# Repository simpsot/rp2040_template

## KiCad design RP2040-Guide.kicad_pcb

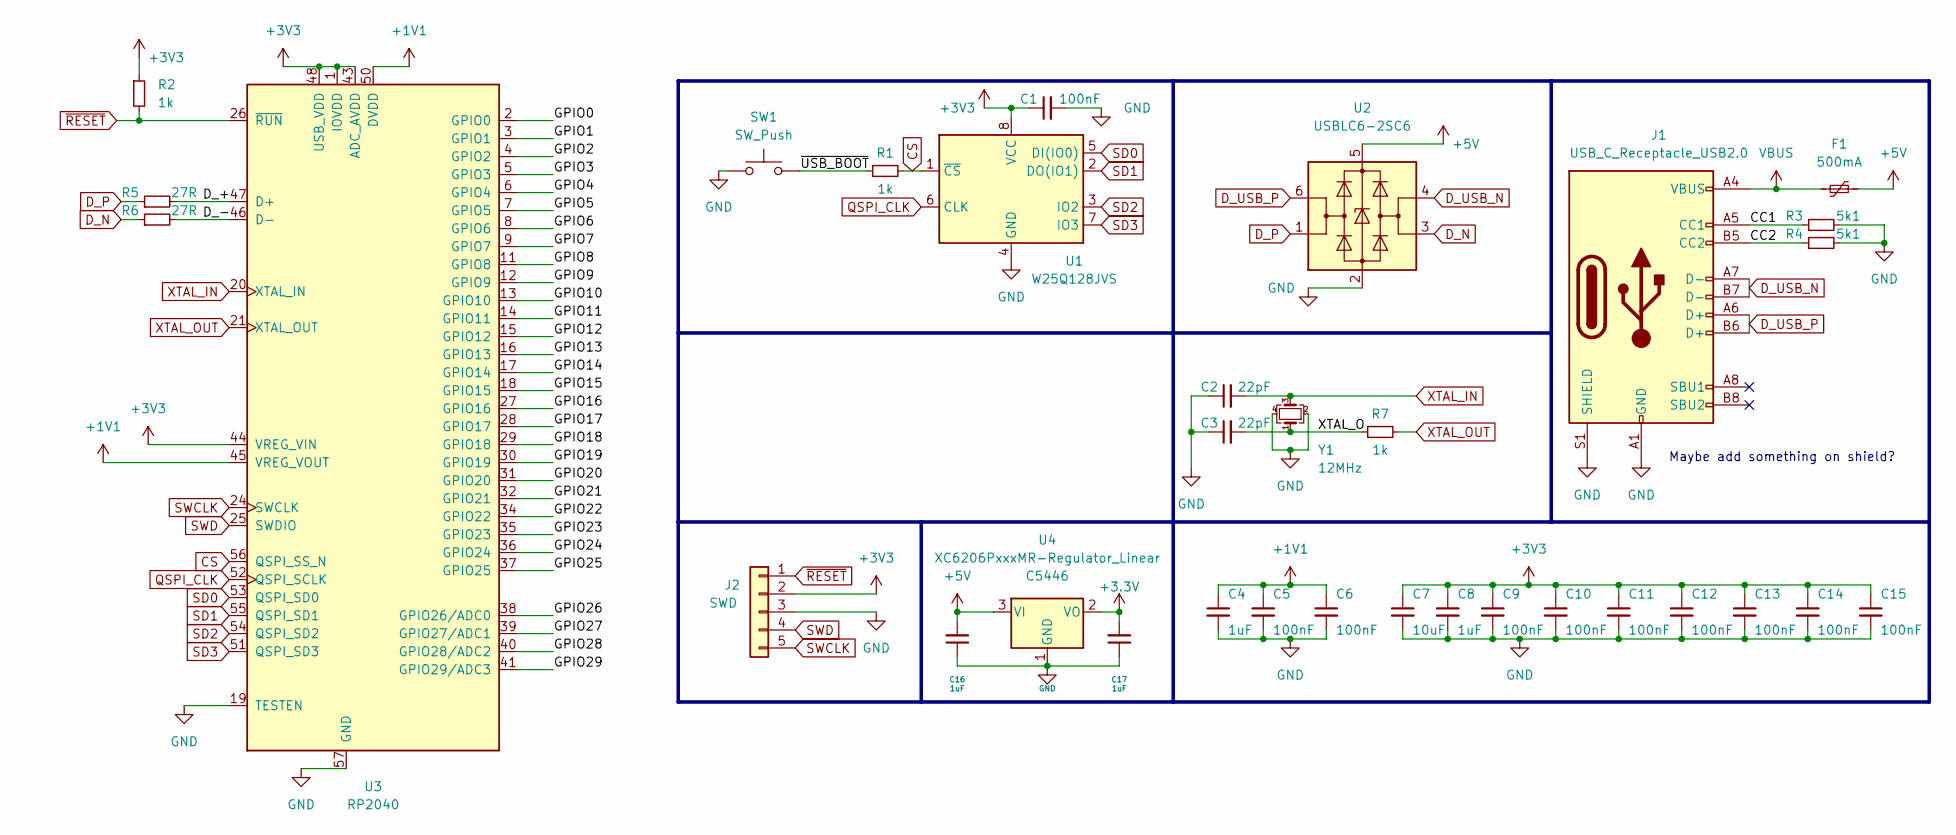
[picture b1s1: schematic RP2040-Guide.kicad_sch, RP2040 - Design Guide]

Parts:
C1, C5, C6, C9, C10, C11, C12, C13, C14, C15: 100nF; C_0402_1005Metric; LCSC C1525
C2, C3: 22pF; C_0402_1005Metric; LCSC C1555
C4, C8, C16, C17: 1uF; C_0402_1005Metric; LCSC C52923
C7: 10uF; C_0402_1005Metric; LCSC C15525
F1: 500mA; Fuse_1206_3216Metric; LCSC C70076
J1: USB_C_Receptacle_USB2.0; USB_C_Receptacle_HRO_TYPE-C-31-M-12; LCSC C165948
J2: SWD; PinSocket_1x05_P2.54mm_Vertical
R1, R2, R7: 1k; R_0402_1005Metric; LCSC C11702
R3, R4: 5k1; R_0402_1005Metric; LCSC C25905
R5, R6: 27R; R_0603_1608Metric; LCSC C25190
SW1: SW_Push; PinSocket_1x02_P2.54mm_Vertical
U1: W25Q128JVS; SOIC-8_5.23x5.23mm_P1.27mm; LCSC C131025
U2: USBLC6-2SC6; SOT-23-6; LCSC C2827654
U3: RP2040; RP2040-QFN-56; LCSC C2040
U4: XC6206PxxxMR-Regulator_Linear; SOT-23; LCSC C5446
Y1: 12MHz; Crystal_SMD_3225-4Pin_3.2x2.5mm; LCSC C9002

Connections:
+1V1: C4.1, C5.1, C6.1, U3.23 (DVDD), U3.45 (VREG_VOUT), U3.50 (DVDD)
+5V: C16.2, F1.2, U2.5 (VBUS), U4.3 (VI)
/CC1: J1.A5 (CC1), R3.1
/CC2: J1.B5 (CC2), R4.1
/D_+: R5.2, U3.47 (D+)
/D_-: R6.2, U3.46 (D-)
/GPIO0: U3.2 (GPIO0)
/GPIO1: U3.3 (GPIO1)
/GPIO2: U3.4 (GPIO2)
/GPIO3: U3.5 (GPIO3)
/GPIO4: U3.6 (GPIO4)
/GPIO5: U3.7 (GPIO5)
/GPIO6: U3.8 (GPIO6)
/GPIO7: U3.9 (GPIO7)
/GPIO8: U3.11 (GPIO8)
/GPIO9: U3.12 (GPIO9)
/GPIO10: U3.13 (GPIO10)
/GPIO11: U3.14 (GPIO11)
/GPIO12: U3.15 (GPIO12)
/GPIO13: U3.16 (GPIO13)
/GPIO14: U3.17 (GPIO14)
/GPIO15: U3.18 (GPIO15)
/GPIO16: U3.27 (GPIO16)
/GPIO17: U3.28 (GPIO17)
/GPIO18: U3.29 (GPIO18)
/GPIO19: U3.30 (GPIO19)
/GPIO20: U3.31 (GPIO20)
/GPIO21: U3.32 (GPIO21)
/GPIO22: U3.34 (GPIO22)
/GPIO23: U3.35 (GPIO23)
/GPIO24: U3.36 (GPIO24)
/GPIO25: U3.37 (GPIO25)
/GPIO26: U3.38 (GPIO26/ADC0)
/GPIO27: U3.39 (GPIO27/ADC1)
/GPIO28: U3.40 (GPIO28/ADC2)
/GPIO29: U3.41 (GPIO29/ADC3)
/XTAL_O: C3.2, R7.1, Y1.1
/~USB_BOOT: R1.1, SW1.2
CS: R1.2, U1.1 (~CS), U3.56 (QSPI_SS_N)
D_N: R6.1, U2.3 (I/O2)
D_P: R5.1, U2.1 (I/O1)
D_USB_N: J1.A7 (D-), J1.B7 (D-), U2.4 (I/O2)
D_USB_P: J1.A6 (D+), J1.B6 (D+), U2.6 (I/O1)
GND: C1.2, C2.1, C3.1, C4.2, C5.2, C6.2, C7.2, C8.2, C9.2, C10.2, C11.2, C12.2, C13.2, C14.2, C15.2, C16.1, C17.1, J1.A1 (GND), J1.A12 (GND), J1.B1 (GND), J1.B12 (GND), J1.S1 (SHIELD), J2.3, R3.2, R4.2, SW1.1, U1.4 (GND), U2.2 (GND), U3.19 (TESTEN), U3.57 (GND), U4.1 (GND), Y1.2, Y1.4
QSPI_CLK: U1.6 (CLK), U3.52 (QSPI_SCLK)
SD0: U1.5 (DI(IO0)), U3.53 (QSPI_SD0)
SD1: U1.2 (DO(IO1)), U3.55 (QSPI_SD1)
SD2: U1.3 (IO2), U3.54 (QSPI_SD2)
SD3: U1.7 (IO3), U3.51 (QSPI_SD3)
SWCLK: J2.5, U3.24 (SWCLK)
SWD: J2.4, U3.25 (SWDIO)
VBUS: F1.1, J1.A4 (VBUS), J1.A9 (VBUS), J1.B4 (VBUS), J1.B9 (VBUS)
XTAL_IN: C2.2, U3.20 (XTAL_IN), Y1.3
XTAL_OUT: R7.2, U3.21 (XTAL_OUT)
~RESET: J2.1, R2.2, U3.26 (~RUN)

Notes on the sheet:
Maybe add something on shield?

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
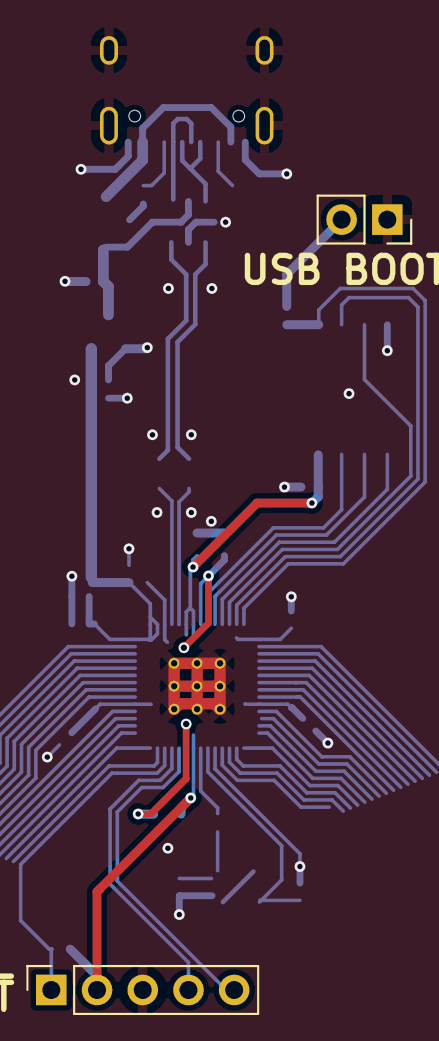
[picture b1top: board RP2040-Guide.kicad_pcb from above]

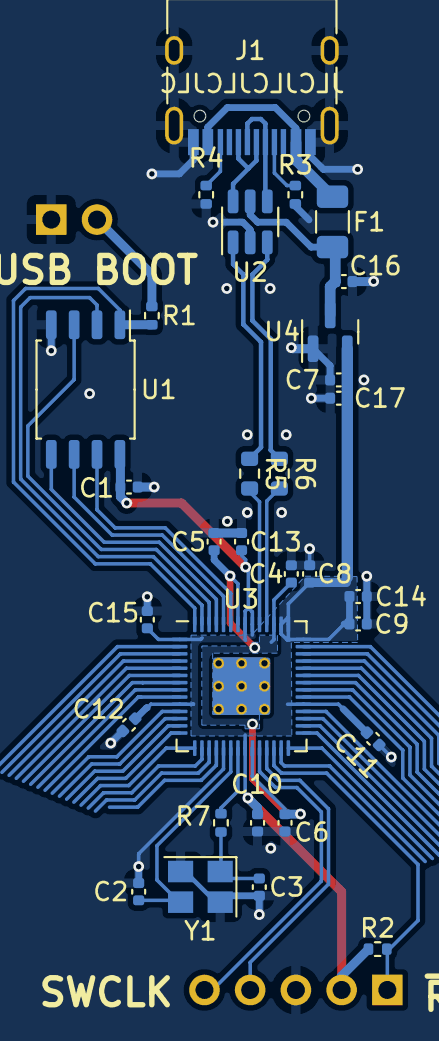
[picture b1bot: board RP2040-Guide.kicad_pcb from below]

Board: 2 copper layers, 33 parts (31 on the bottom side), 26 nets.
